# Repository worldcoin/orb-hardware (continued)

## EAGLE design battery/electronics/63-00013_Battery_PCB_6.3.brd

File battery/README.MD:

## Overview
Our exchangeable battery is responsible for powering the orb during the dayli operations. Key facts: 
* **Cell**: 8x 18650 Li-Ion cells 
* **Configuration**: 4SP2 (4 in series, 2 strings parallel)
* **Nominal voltage**: 14.8V
* **Capacity**: 96.48Wh
* **Charging interface**: USB-C
* **Other**: UN38.3 certified

## Mechanics

You can download the .stp-files [here](mechanics/download.sh).

Preview STP-File:

## Electronics

Preview battery circuit board:

## Bill of material structure
Part of our release is a drilled-down bill of material listing all the parts used in our device. 

The columns in that file are: 
* **Level**: Due to multiple assemblies in our device, we have a nested BOM. The level column tells you how deep this component is nested.
* **Item number**: Running number within the Assembly / Sub-Assembly
* **Partnumber**: Our internal part-number
* **Manufacturer P/N**: The part-number / unique name that our supplier uses as a part reference
* **Quantity**: Quantity of the part in the given assembly context

Please note that some parts have multiple entries in our BOM as each line lists the component in a different assembly context. 

## Directory Structure

    ├── Electronics         # Board and schematics
    ├── Mechanics           # STP-Files
    └── BOM                 # Bill of material   

## License

Copyright 2020-2023 The Worldcoin Foundation.

You may use this package under the Worldcoin Responsible Use License, version 1.0, or at your option, any later version. See the file [COPYING](../COPYING.md) for more details, and [LICENSE](../LICENSE.md) for the terms of the Worldcoin Responsible Use License, version 1.0.

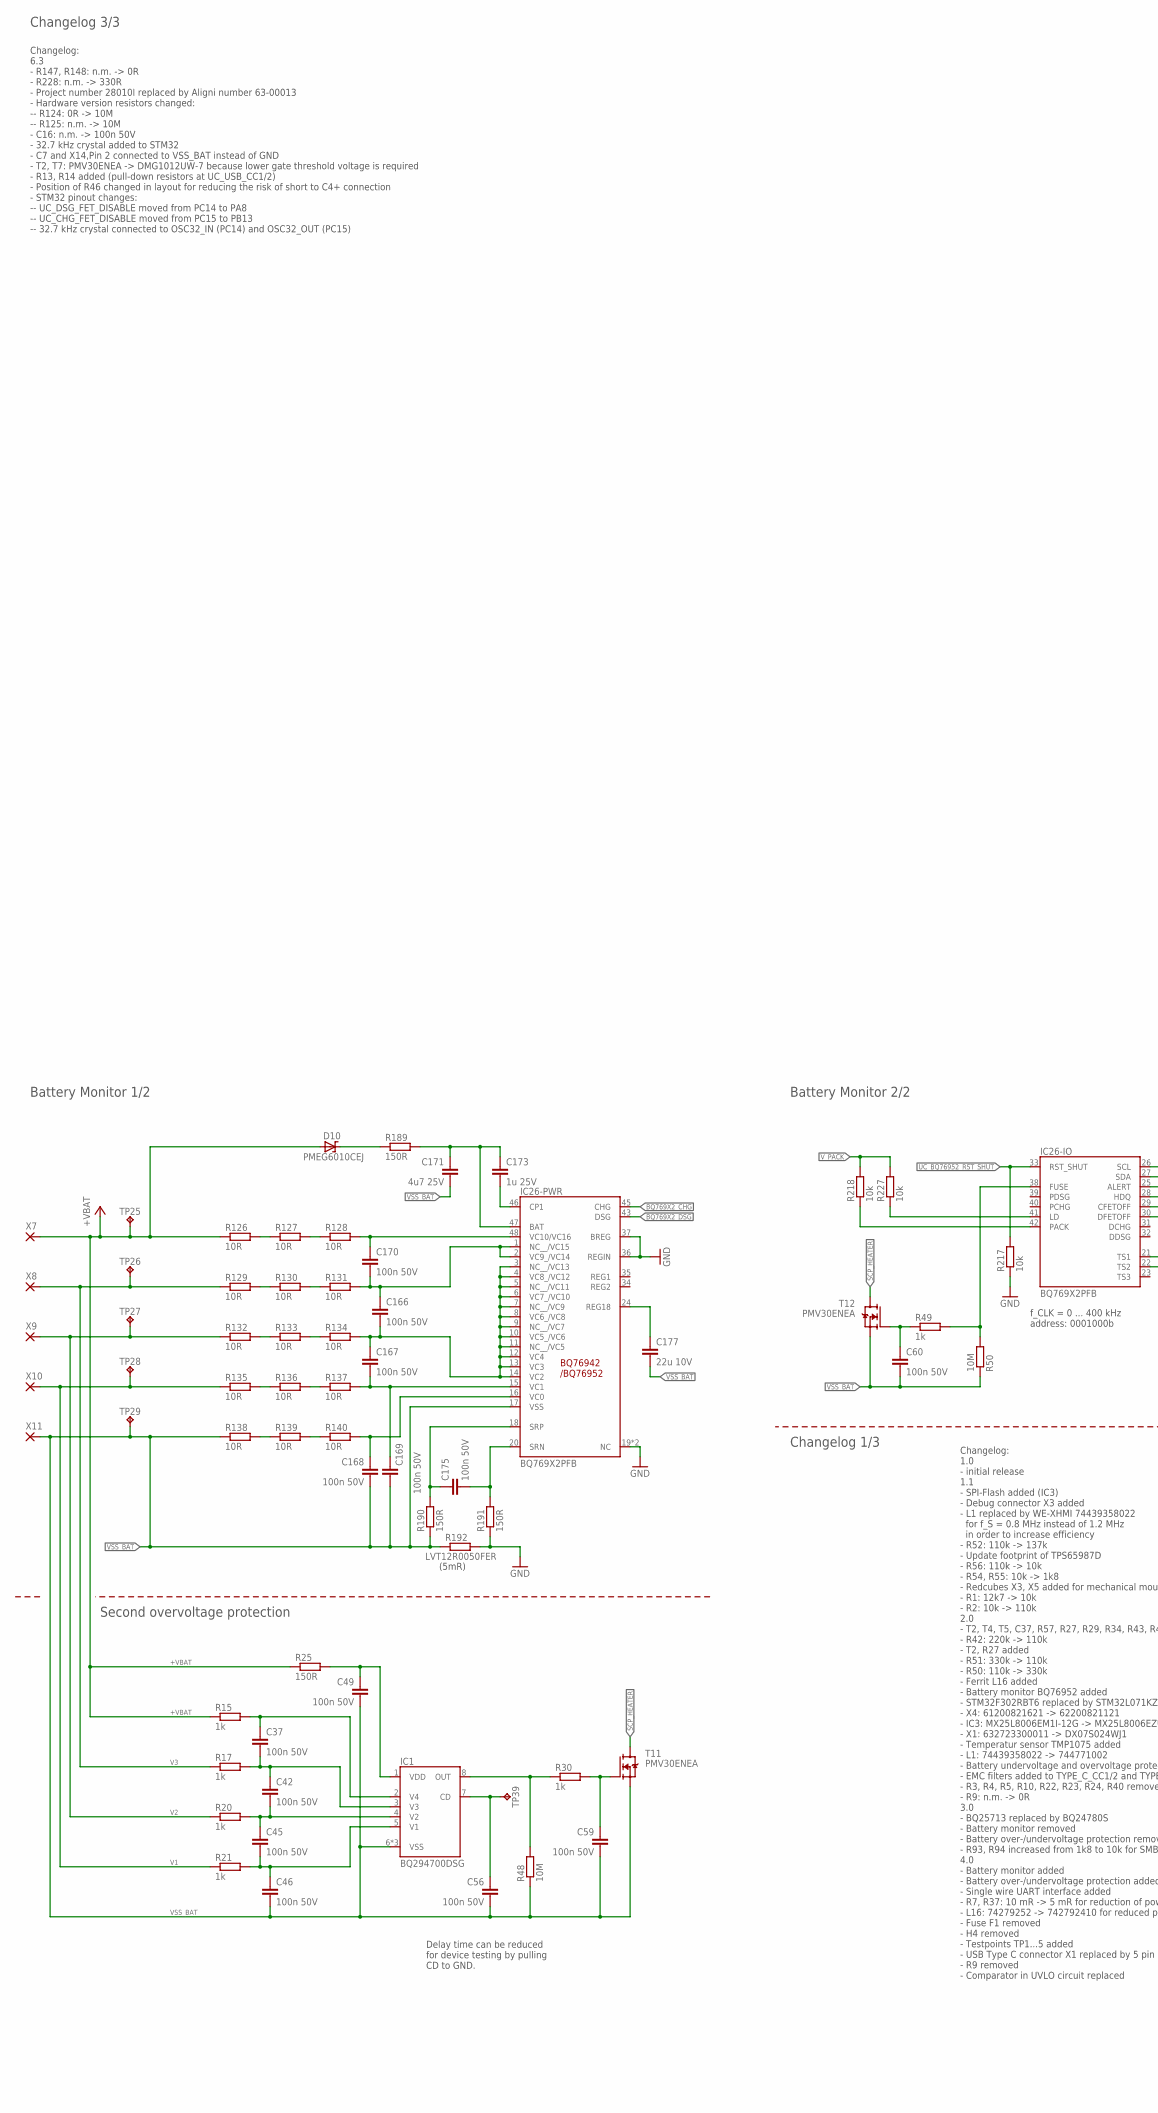
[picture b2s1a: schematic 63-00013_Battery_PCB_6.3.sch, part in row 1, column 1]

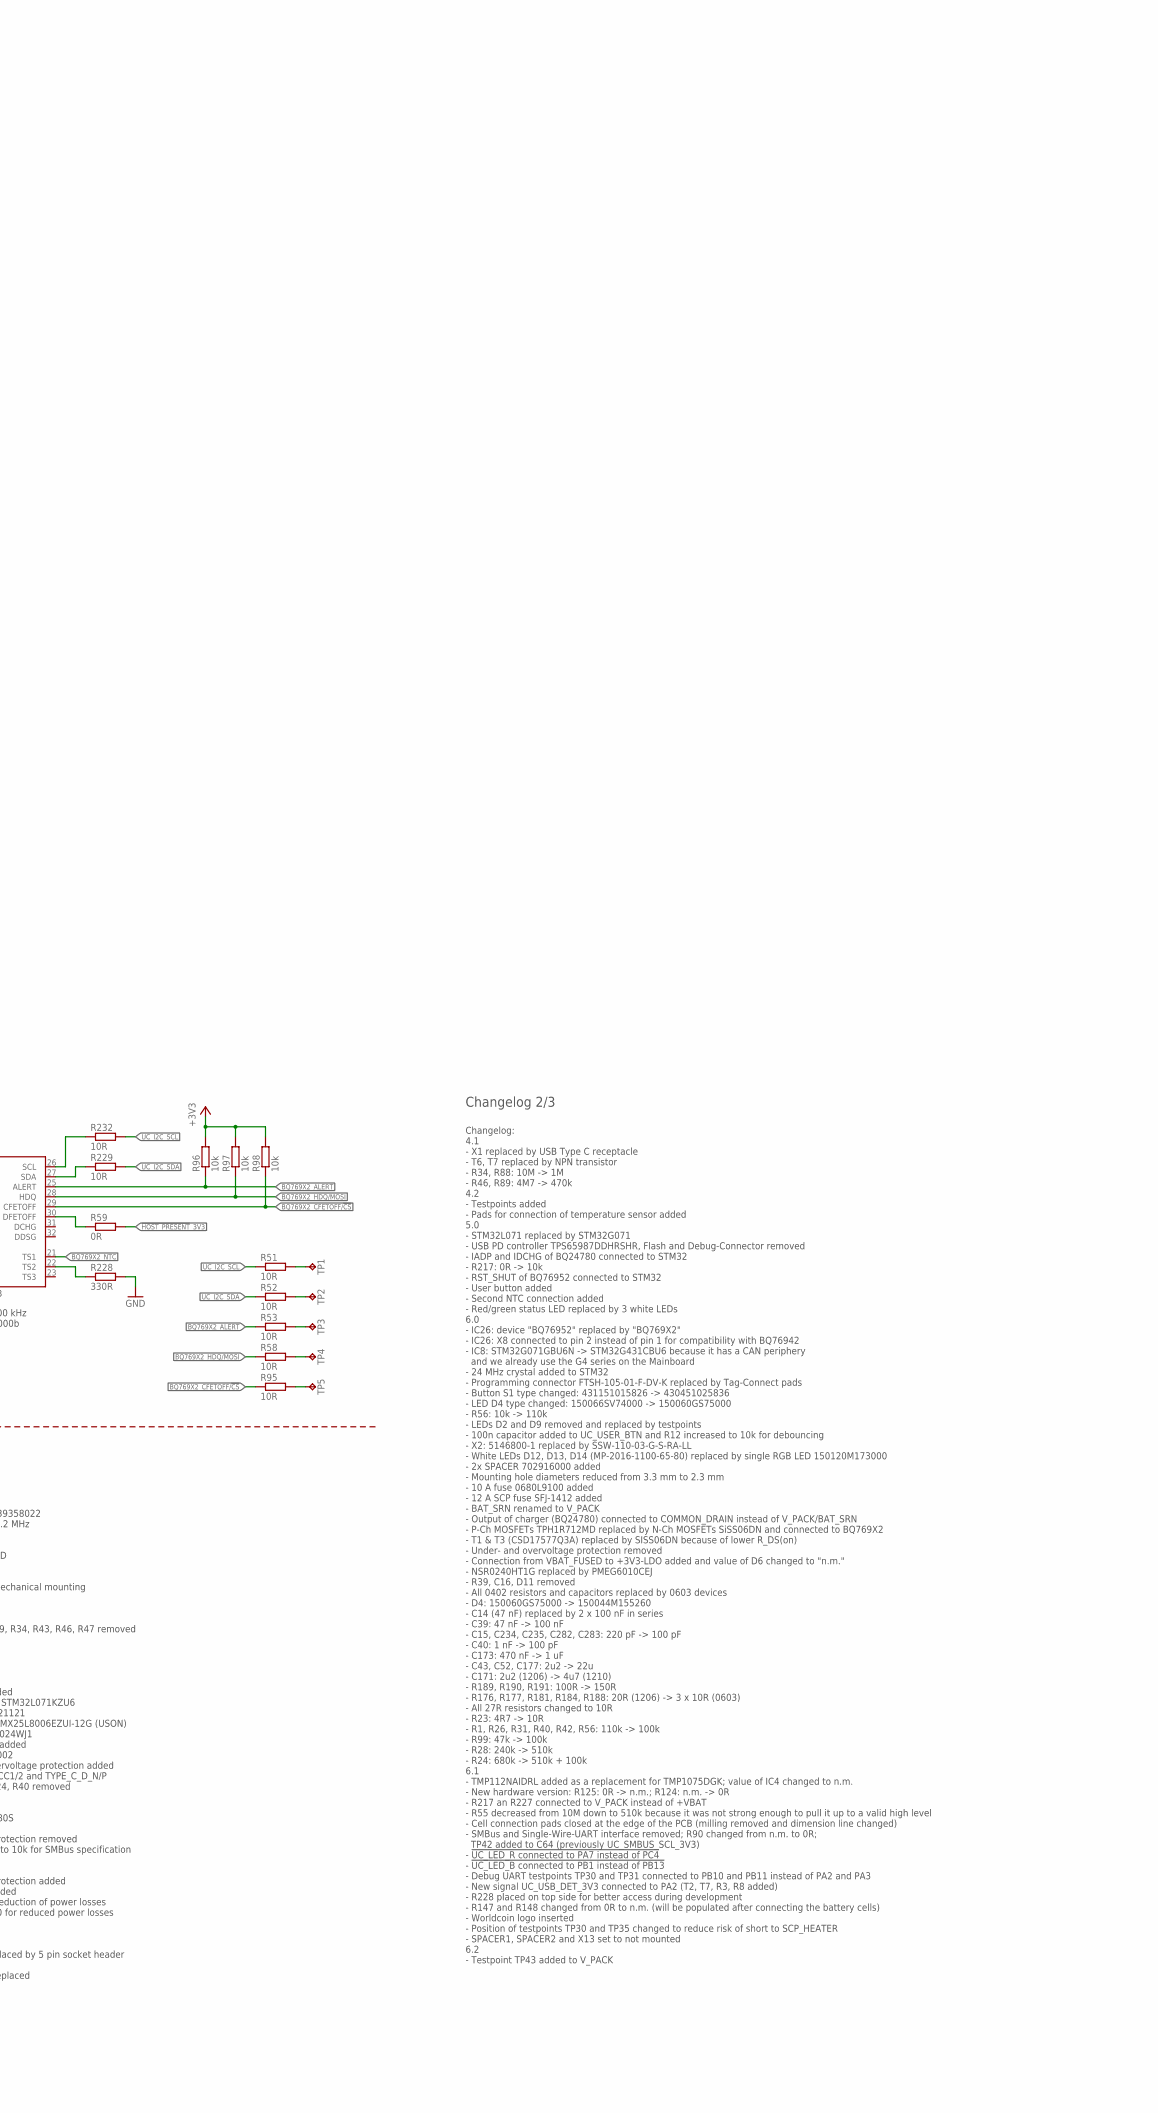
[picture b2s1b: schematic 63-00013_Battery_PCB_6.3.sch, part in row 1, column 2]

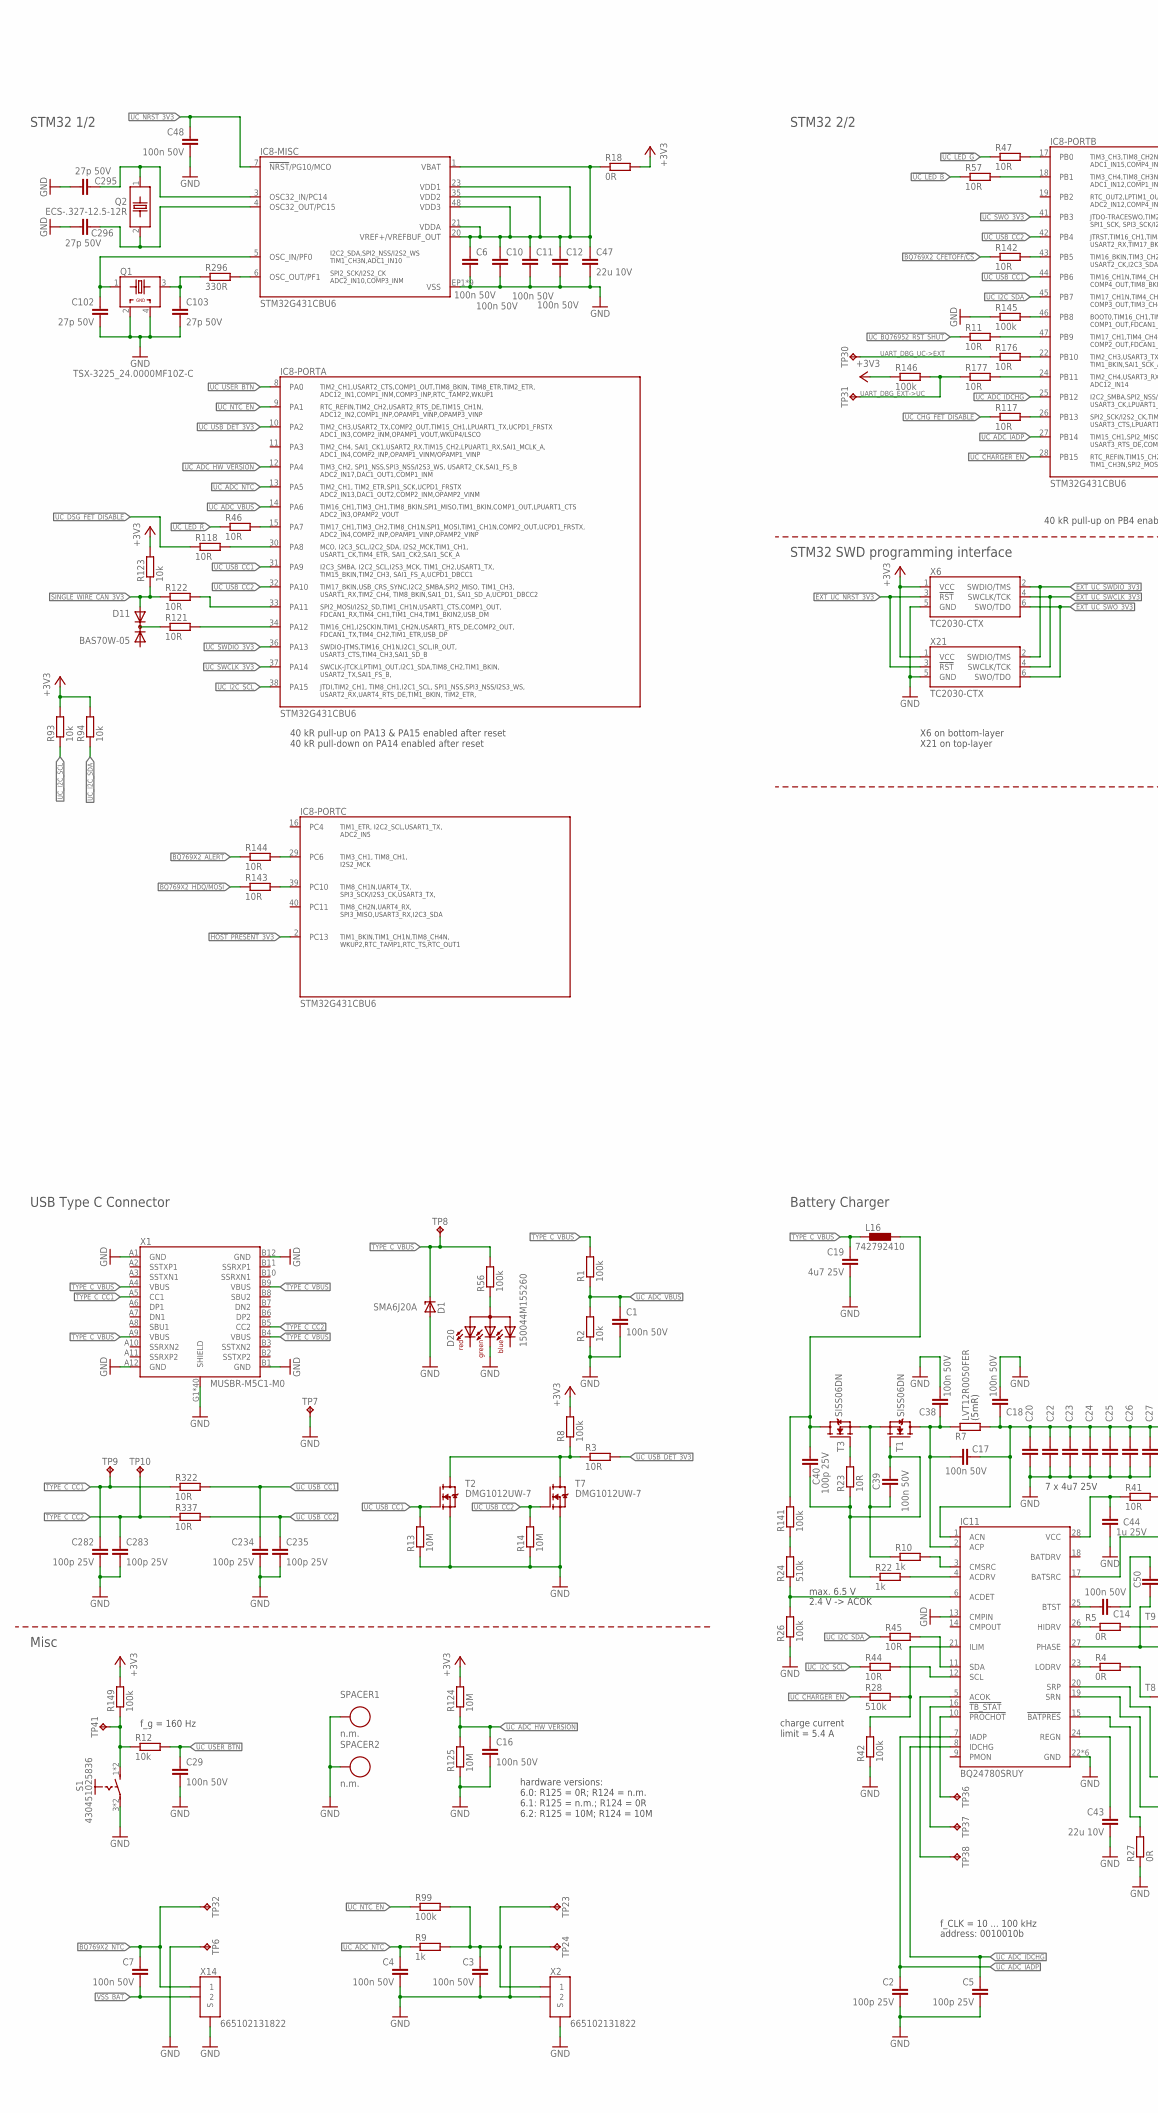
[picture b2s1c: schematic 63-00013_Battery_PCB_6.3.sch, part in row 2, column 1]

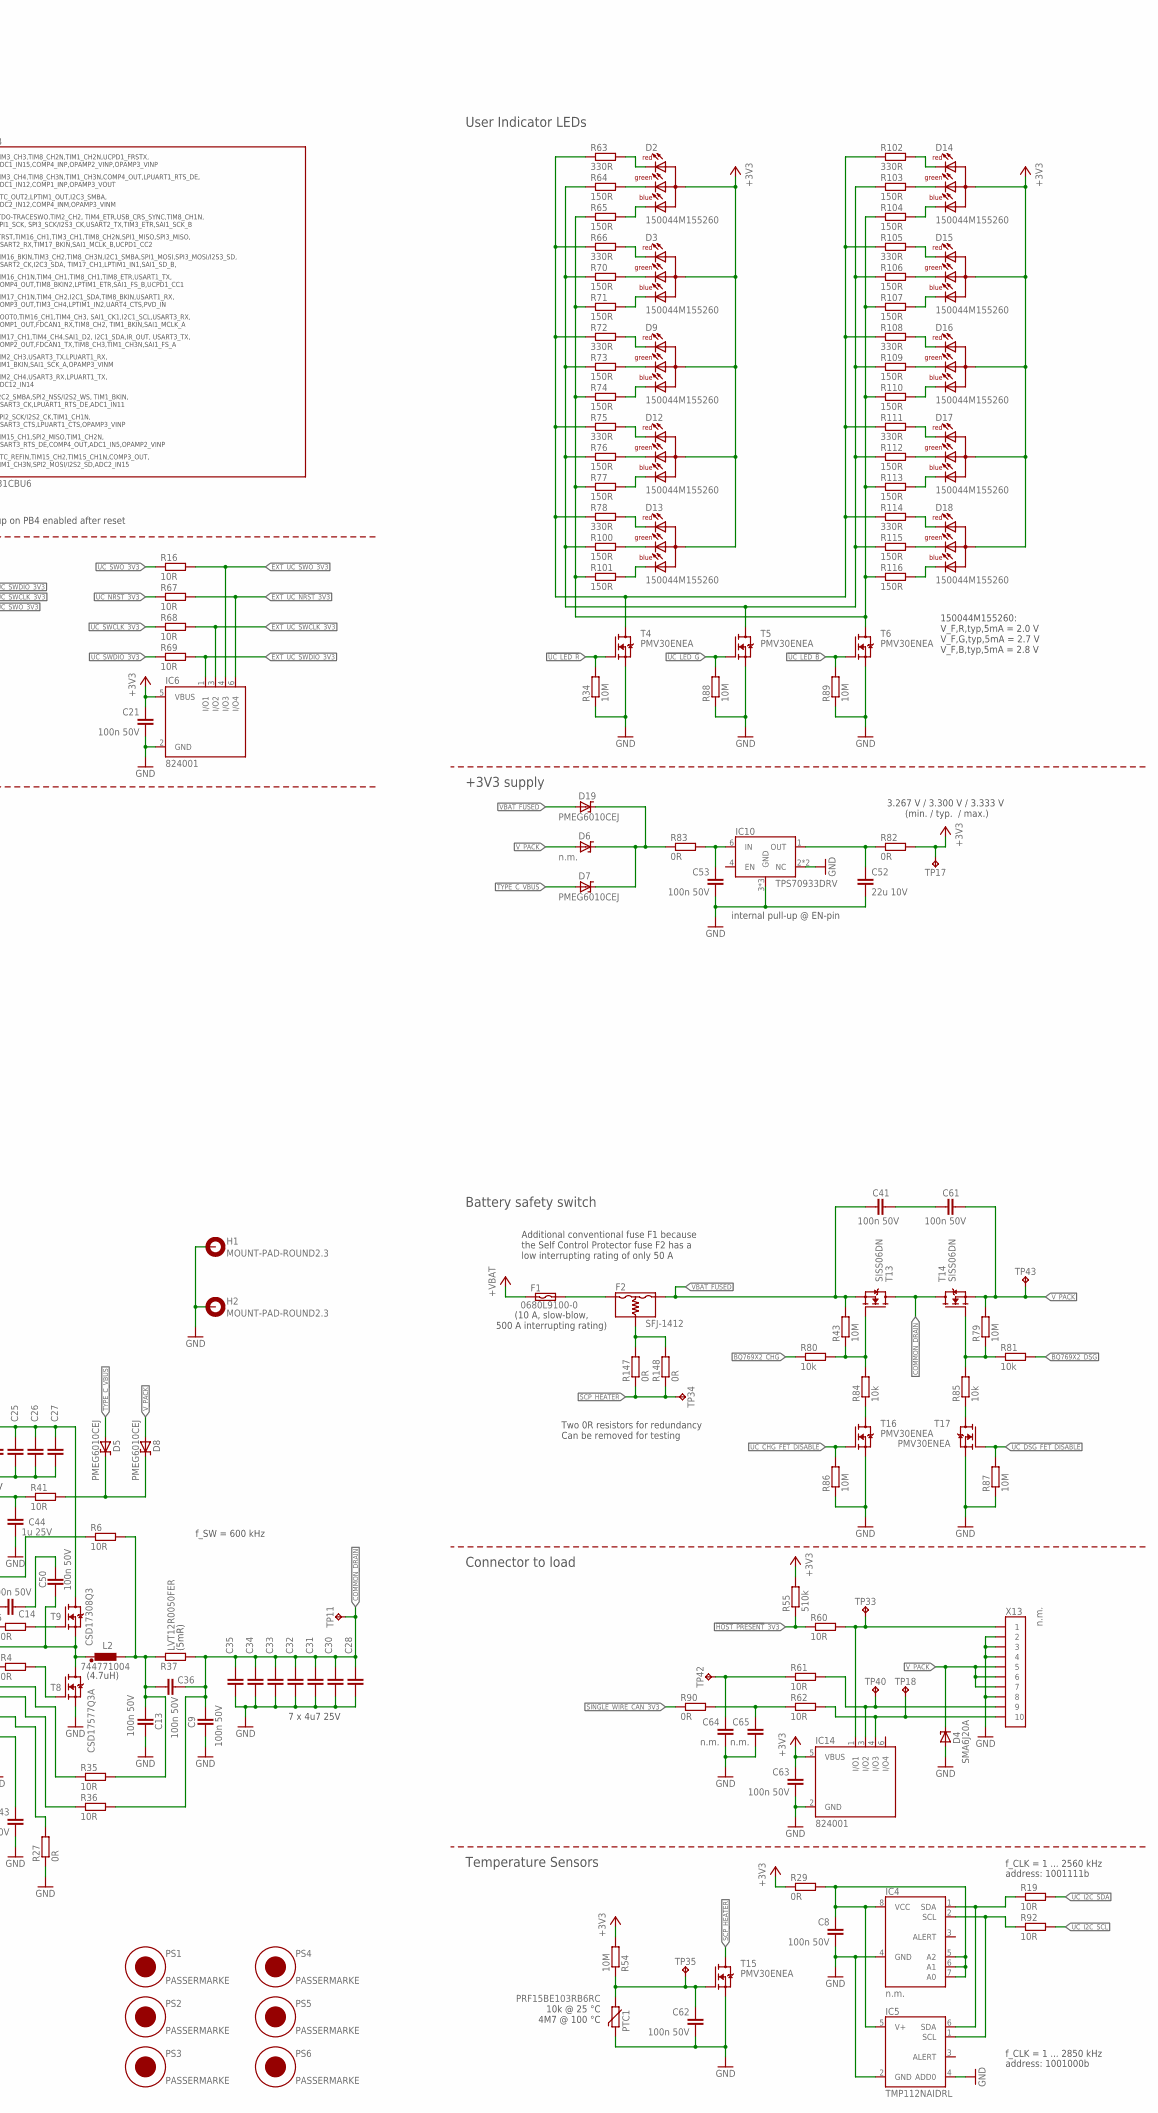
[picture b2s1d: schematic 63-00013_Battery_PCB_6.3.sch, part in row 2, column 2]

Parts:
C1, C3, C4, C6, C7, C8, C9, C10, C11, C12, C13, C14, C16, C17, C18, C21, C29, C36, C37, C38, C39, C41, C42, C45, C46, C48, C49, C50, C53, C56, C59, C60, C61, C62, C63, C166, C167, C168, C169, C170, C175: 100n 50V; C0603; VOLTAGE 50.0 V
C2, C5, C40, C234, C235, C282, C283: 100p 25V; C0603; VOLTAGE 25.0 V
C19, C20, C22, C23, C24, C25, C26, C27, C28, C30, C31, C32, C33, C34, C35, C171: 4u7 25V; C1210; VOLTAGE 25 V
C43, C47, C52, C177: 22u 10V; C0805; VOLTAGE 10.0 V
C44, C173: 1u 25V; C0805; VOLTAGE 25.0 V
C64, C65: n.m.; C0603; VOLTAGE 25.0 V
C102, C103, C295, C296: 27p 50V; C0603; VOLTAGE 50.0 V
D1, D4: SMA6J20A; SMA_ST
D2, D3, D9, D12, D13, D14, D15, D16, D17, D18, D20: 150044M155260; 150044M155260_WUERTH
D5, D7, D8, D10, D19: PMEG6010CEJ; SOD323F_SC-90_NXP
D6: n.m.; SOD323F_SC-90_NXP
D11: BAS70W-05; SOT-323_DIODES_INC
F1: 0680L9100-0; 0680L_BEL_FUSE
F2: SFJ-1412; SFJ-XX12_DEXERIALS
H1, H2: MOUNT-PAD-ROUND2.3; 2,3-PAD
IC1: BQ294700DSG; DSG0008A_WSON_TI
IC4: n.m.; S-PDSO-G8_DGK_VSSOP_TI
IC5: TMP112NAIDRL; DRL0006A_TI
IC6, IC14: 824001; SOT23-6L_WE
IC8: STM32G431CBU6; UFQFPN48_ST
IC10: TPS70933DRV; DRV0006A_TI
IC11: BQ24780SRUY; RUY0028A_TI
IC26: BQ769X2PFB; S-PQFP-G48_PFB_TI
L2: 744771004; WE-PD_1260_WE
L16: 742792410; FERRIT_1806_WUERTH
PS1, PS2, PS3, PS4, PS5, PS6: PASSERMARKE
PTC1: PRF15BE103RB6RC; R0402
Q1: TSX-3225_24.0000MF10Z-C; TSX-3225_SEIKO_EPSON
Q2: ECS-.327-12.5-12R; ECX-12R_ECS
R1, R8, R26, R42, R56, R99, R141, R145, R146, R149: 100k; R0603
R2, R12, R80, R81, R84, R85, R93, R94, R96, R97, R98, R123, R217, R218, R227: 10k; R0603
R3, R6, R11, R16, R19, R23, R35, R36, R41, R44, R45, R46, R47, R51, R52, R53, R57, R58, R60, R61, R62, R67, R68, R69, R92, R95, R117, R118, R121, R122, R126, R127, R128, R129, R130, R131, R132, R133, R134, R135, R136, R137, R138, R139, R140, R142, R143, R144, R176, R177, R229, R232, R322, R337: 10R; R0603
R4, R5, R18, R27, R29, R59, R82, R83, R90, R147, R148: 0R; R0603
R7, R37, R192: LVT12R0050FER; LVT12_R003_OHMITE
R9, R10, R15, R17, R20, R21, R22, R30, R49: 1k; R0603
R13, R14, R34, R43, R48, R50, R54, R79, R86, R87, R88, R89, R124, R125: 10M; R0603
R24, R28, R55: 510k; R0603
R25, R64, R65, R70, R71, R73, R74, R76, R77, R100, R101, R103, R104, R106, R107, R109, R110, R112, R113, R115, R116, R189, R190, R191: 150R; R0603
R63, R66, R72, R75, R78, R102, R105, R108, R111, R114, R228, R296: 330R; R0603
S1: 430451025836; 430451025836_WUERTH
SPACER1, SPACER2: n.m.; 702916000_WUERTH
T1, T3, T13, T14: SISS06DN; POWERPAK_1212-8S_VISHAY
T2, T7: DMG1012UW-7; SOT-323_DIODES_INC
T4, T5, T6, T11, T12, T15, T16, T17: PMV30ENEA; SOT-23_NXP
T8: CSD17577Q3A; Q3A_TI
T9: CSD17308Q3; Q3_TI
TP1, TP2, TP3, TP4, TP5, TP6, TP7, TP8, TP9, TP10, TP11, TP17, TP18, TP23, TP24, TP25, TP26, TP27, TP28, TP29, TP30, TP31, TP32, TP33, TP34, TP35, TP36, TP37, TP38, TP39, TP40, TP41, TP42, TP43: TESTPOINT_VIA_ROUND_0.8MM; TESTVIA_ROUND_0.8MM
X1: MUSBR-M5C1-M0; MUSBR-M5C1-XX_AMPHENOL
X2, X14: 665102131822; 665102131822_WURTH
X6, X21: TC2030-CTX; TC2030-IDC-FP_TAGCONNECT
X7, X8, X9, X10, X11: WIREPAD_0.8X6.5MM
X13: n.m.; SSW-110-03-G-S-RA-LL_SAMTEC

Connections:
!HOST_PRESENT!_3V3: IC8.2 (PC13), R55.1, R59.2, R60.1
!LED_B: R65.1, R71.1, R74.1, R77.1, R101.1, R104.1, R107.1, R110.1, R113.1, R116.1, T6.3 (D)
!LED_G: R64.1, R70.1, R73.1, R76.1, R100.1, R103.1, R106.1, R109.1, R112.1, R115.1, T5.3 (D)
!LED_R: R63.1, R66.1, R72.1, R75.1, R78.1, R102.1, R105.1, R108.1, R111.1, R114.1, T4.3 (D)
!UC_LED_B: R57.1, R89.2, T6.1 (G)
!UC_LED_G: R47.1, R88.2, T5.1 (G)
!UC_LED_R: R34.2, R46.1, T4.1 (G)
+3V3: C21.1, C63.1, D2.1 (A), D3.1 (A), D9.1 (A), D12.1 (A), D13.1 (A), D14.1 (A), D15.1 (A), D16.1 (A), D17.1 (A), D18.1 (A), IC6.5 (VBUS), IC14.5 (VBUS), R8.2, R18.2, R29.1, R54.2, R55.2, R82.2, R93.2, R94.2, R96.2, R97.2, R98.2, R123.2, R124.2, R146.1, R149.2, TP17.P$1, X6.1 (VCC), X21.1 (VCC)
+VBAT: D10.A, F1.1, R15.1, R25.1, R126.1, TP25.P$1, X7.P$1, X7.P$2, X7.P$3, X7.P$4, X7.P$5, X7.P$6, X7.P$7, X7.P$8, X7.P$9, X7.P$10, X7.P$11, X7.P$12, X7.P$13, X7.P$14, X7.P$15, X7.P$16, X7.P$17, X7.P$18, X7.P$19, X7.P$20, X7.P$21, X7.P$22, X7.P$23, X7.P$24, X7.P$25, X7.P$26, X7.P$27, X7.P$28, X7.P$29, X7.P$30, X7.P$31, X7.P$32, X7.P$33, X7.P$34, X7.P$35, X7.P$36, X7.P$37, X7.P$38, X7.P$39, X7.P$40, X7.P$41, X7.P$42, X7.P$43, X7.P$44, X7.P$45, X7.P$46, X7.P$47, X7.P$48, X7.P$49, X7.P$50, X7.P$51, X7.P$52, X7.P$53, X7.P$54, X7.P$55, X7.P$56, X7.P$57, X7.P$58, X7.P$59, X7.P$60, X7.P$61, X7.P$62, X7.P$63, X7.P$64, X7.P$65, X7.P$66, X7.P$67
BQ769X2_ALERT: IC26.25 (ALERT), R53.1, R96.1, R144.1
BQ769X2_CFETOFF/!CS: IC26.29 (CFETOFF), R95.1, R98.1, R142.1
BQ769X2_CHG: IC26.45 (CHG), R80.1
BQ769X2_DSG: IC26.43 (DSG), R81.2
BQ769X2_HDQ/MOSI: IC26.28 (HDQ), R58.1, R97.1, R143.1
BQ769X2_NTC: C7.1, IC26.21 (TS1), TP32.P$1, X14.1
CHARGER_VCC: D6.C, D7.C, D19.C, R83.1
COMMON_DRAIN: C9.1, C28.1, C30.1, C31.1, C32.1, C33.1, C34.1, C35.1, C36.2, R36.2, R37.2, T13.5 (D), T14.5 (D), TP11.P$1
EXT_UC_NRST_3V3: IC6.6 (I/O4), R67.2, X6.3 (!RST), X21.3 (!RST)
EXT_UC_SWCLK_3V3: IC6.3 (I/O2), R68.2, X6.4 (SWCLK/TCK), X21.4 (SWCLK/TCK)
EXT_UC_SWDIO_3V3: IC6.1 (I/O1), R69.2, X6.2 (SWDIO/TMS), X21.2 (SWDIO/TMS)
EXT_UC_SWO_3V3: IC6.4 (I/O3), R16.2, X6.6 (SWO/TDO), X21.6 (SWO/TDO)
GND: C1.2, C2.2, C3.2, C4.2, C5.2, C6.2, C8.2, C9.2, C10.2, C11.2, C12.2, C13.2, C16.2, C18.1, C19.2, C20.2, C21.2, C22.2, C23.2, C24.2, C25.2, C26.2, C27.2, C28.2, C29.2, C30.2, C31.2, C32.2, C33.2, C34.2, C35.2, C38.1, C43.2, C44.2, C47.2, C48.2, C52.2, C53.2, C62.2, C63.2, C64.2, C65.2, C102.2, C103.2, C234.2, C235.2, C282.2, C283.2, C295.2, C296.2, D1.A, D4.A, D20.3 (C_GREEN), H1.B2,3, H2.B2,3, IC4.4 (GND), IC5.2 (GND), IC5.4 (ADD0), IC6.2 (GND), IC8.EP1 (VSS), IC8.EP2 (VSS), IC8.EP3 (VSS), IC8.EP4 (VSS), IC8.EP5 (VSS), IC8.EP6 (VSS), IC8.EP7 (VSS), IC8.EP8 (VSS), IC8.EP9 (VSS), IC10.2 (NC), IC10.3 (GND), IC10.5 (NC), IC10.7.1 (GND), IC10.7.2 (GND), IC11.13 (CMPIN), IC11.22 (GND), IC11.E1 (GND), IC11.E2 (GND), IC11.E3 (GND), IC11.E4 (GND), IC11.E5 (GND), IC14.2 (GND), IC26.19 (NC), IC26.36 (REGIN), IC26.37 (BREG), IC26.44 (NC), PTC1.1, Q1.2 (G1), Q1.4 (G2), R2.1, R13.1, R14.1, R26.1, R27.1, R34.1, R42.1, R86.1, R87.1, R88.1, R89.1, R125.1, R145.1, R191.1, R192.2, R217.1, R228.2, S1.3, S1.4, SPACER1.P$1, SPACER2.P$1, T2.2 (S), T4.2 (S), T5.2 (S), T6.2 (S), T7.2 (S), T8.1 (S), T8.2 (S), T8.3 (S), T15.2 (S), T16.2 (S), T17.2 (S), TP6.P$1, TP7.P$1, TP24.P$1, X1.A1 (GND), X1.A12 (GND), X1.B1 (GND), X1.B12 (GND), X1.G1 (SHIELD), X1.G2 (SHIELD), X1.G3 (SHIELD), X1.G4 (SHIELD), X1.G5 (SHIELD), X1.G6 (SHIELD), X1.S1 (SHIELD), X1.S2 (SHIELD), X1.S3 (SHIELD), X1.S4 (SHIELD), X1.S5 (SHIELD), X1.S6 (SHIELD), X1.S7 (SHIELD), X1.S8 (SHIELD), X1.S9 (SHIELD), X1.S10 (SHIELD), X1.S11 (SHIELD), X1.S12 (SHIELD), X1.S13 (SHIELD), X1.S14 (SHIELD), X1.S15 (SHIELD), X1.S16 (SHIELD), X1.S17 (SHIELD), X1.S18 (SHIELD), X1.S19 (SHIELD), X1.S20 (SHIELD), X1.S21 (SHIELD), X1.S22 (SHIELD), X1.S23 (SHIELD), X1.S24 (SHIELD), X1.S25 (SHIELD), X1.S26 (SHIELD), X1.S27 (SHIELD), X1.S28 (SHIELD), X1.S29 (SHIELD), X1.S30 (SHIELD), X1.S31 (SHIELD), X1.S32 (SHIELD), X1.S33 (SHIELD), X1.S34 (SHIELD), X2.2, X2.S1 (S), X2.S2 (S), X6.5 (GND), X13.2, X13.3, X13.4, X13.8, X14.S1 (S), X14.S2 (S), X21.5 (GND)
unnamed: C64.1, R61.1, TP42.P$1
unnamed: D5.C, D8.C, R41.2
unnamed: R12.1, R149.1, S1.1 (S), S1.2 (S), TP41.P$1
unnamed: IC8.15 (PA7), R46.2
unnamed: IC8.47 (PB9), R11.2
unnamed: IC8.18 (PB1), R57.2
unnamed: D11.3 (C), R121.1
unnamed: C103.1, Q1.3 (C2), R296.1
unnamed: IC11.10 (!PROCHOT), TP36.P$1
unnamed: IC11.16 (!TB_STAT), TP37.P$1
unnamed: IC11.5 (ACOK), TP38.P$1
unnamed: C45.2, C46.1, IC1.5 (V1), R21.2
unnamed: C42.2, C45.1, IC1.4 (V2), R20.2
unnamed: C37.2, C42.1, IC1.3 (V3), R17.2
unnamed: C37.1, IC1.2 (V4), R15.2
unnamed: C49.1, IC1.1 (VDD), R25.2
unnamed: C56.1, IC1.7 (CD), TP39.P$1
unnamed: IC1.8 (OUT), R30.1, R48.2
unnamed: F1.2, F2.T1 (F1)
unnamed: C59.1, R30.2, T11.1 (G)
unnamed: C14.2, IC11.25 (BTST)
unnamed: C60.1, R49.1, T12.1 (G)
unnamed: IC4.2 (SCL), IC5.1 (SCL), R92.1
unnamed: IC11.17 (BATSRC), R6.1
unnamed: C17.1, C38.2, IC11.2 (ACP), R7.1, T1.5 (D)
unnamed: C13.1, C36.1, L2.NODOT, R6.2, R35.2, R37.1
unnamed: C17.2, C18.2, C20.1, C22.1, C23.1, C24.1, C25.1, C26.1, C27.1, IC11.1 (ACN), R7.2, T9.5 (D), T9.P$1 (D), T9.P$4 (D), T9.P$5 (D), T9.P$6 (D), T9.P$7 (D)
unnamed: IC11.4 (ACDRV), R22.2
unnamed: IC11.3 (CMSRC), R10.2
unnamed: C39.1, R10.1, T1.1 (S), T1.2 (S), T1.3 (S), T3.1 (S), T3.2 (S), T3.3 (S)
unnamed: C39.2, C40.1, R22.1, R23.1, T1.4 (G)
unnamed: IC26.38 (FUSE), R49.2, R50.2
unnamed: C8.1, IC4.5 (A2), IC4.6 (A1), IC4.7 (A0), IC4.8 (VCC), IC5.5 (V+), R29.2
unnamed: C62.1, PTC1.2, R54.1, T15.1 (G), TP35.P$1
unnamed: IC26.30 (DFETOFF), R59.1
unnamed: C40.2, L16.1, R141.2, T3.5 (D)
unnamed: C41.1, C61.2
unnamed: IC14.1 (I/O1), R60.2, TP33.P$1, X13.1
unnamed: C6.1, C10.1, C11.1, C12.1, C47.1, IC8.1 (VBAT), IC8.20 (VREF+/VREFBUF_OUT), IC8.21 (VDDA), IC8.23 (VDD1), IC8.35 (VDD2), IC8.48 (VDD3), R18.1
unnamed: IC11.19 (SRN), R36.1
unnamed: IC11.20 (SRP), R35.1
unnamed: R5.2, T9.4 (G)
unnamed: R23.2, T3.4 (G)
unnamed: IC11.12 (SCL), R44.2
unnamed: IC11.11 (SDA), R45.2
unnamed: IC11.6 (ACDET), R24.1, R26.2
unnamed: IC11.21 (ILIM), R28.2, R42.2
unnamed: IC14.3 (I/O2), R61.2, TP40.P$1, X13.9
unnamed: IC14.4 (I/O3), R62.2, TP18.P$1, X13.10
unnamed: IC11.15 (!BATPRES), R27.2
unnamed: C50.2, IC11.27 (PHASE), L2.DOT, T8.5 (D), T8.P$1 (D), T8.P$2 (D), T8.P$3 (D), T8.P$4 (D), T8.P$5 (D), T8.P$6 (D), T8.P$7 (D), T9.1 (S), T9.2 (S), T9.3 (S)
unnamed: IC8.34 (PA12), R121.2
unnamed: C44.1, IC11.28 (VCC), R41.1
unnamed: C65.1, R62.1, R90.2
unnamed: C43.1, IC11.24 (REGN)
unnamed: C168.1, IC26.16 (VC0), R140.2
unnamed: C177.1, IC26.24 (REG18)
unnamed: IC8.22 (PB10), R176.2
unnamed: IC8.24 (PB11), R177.2
unnamed: IC8.33 (PA11), R122.2
unnamed: D2.3 (C_GREEN), R64.2
unnamed: D2.2 (C_RED), R63.2
unnamed: D20.1 (A), R56.1
unnamed: R127.2, R128.1
unnamed: R43.1, R80.2, R84.2, T13.4 (G)
unnamed: D2.4 (C_BLUE), R65.2
unnamed: D3.3 (C_GREEN), R70.2
unnamed: D3.2 (C_RED), R66.2
unnamed: D3.4 (C_BLUE), R71.2
unnamed: D9.3 (C_GREEN), R73.2
unnamed: D9.2 (C_RED), R72.2
unnamed: D9.4 (C_BLUE), R74.2
unnamed: R79.1, R81.1, R85.2, T14.4 (G)
unnamed: C52.1, IC10.1 (OUT), R82.1
unnamed: C53.1, IC10.6 (IN), R83.2
unnamed: R85.1, T17.3 (D)
unnamed: R84.1, T16.3 (D)
unnamed: C14.1, C50.1
unnamed: R126.2, R127.1
unnamed: IC4.1 (SDA), IC5.6 (SDA), R19.1
unnamed: R130.2, R131.1
unnamed: IC11.26 (HIDRV), R5.1
unnamed: IC11.23 (LODRV), R4.1
unnamed: R4.2, T8.4 (G)
unnamed: R95.2, TP5.P$1
unnamed: R58.2, TP4.P$1
unnamed: R53.2, TP3.P$1
unnamed: R52.2, TP2.P$1
unnamed: R51.2, TP1.P$1
unnamed: C3.1, R9.2, R99.2, TP23.P$1, X2.1
unnamed: D12.3 (C_GREEN), R76.2
unnamed: R129.2, R130.1
unnamed: D12.2 (C_RED), R75.2
unnamed: D12.4 (C_BLUE), R77.2
unnamed: D13.3 (C_GREEN), R100.2
unnamed: D13.2 (C_RED), R78.2
unnamed: D13.4 (C_BLUE), R101.2
unnamed: D14.3 (C_GREEN), R103.2
unnamed: D14.2 (C_RED), R102.2
unnamed: D14.4 (C_BLUE), R104.2
unnamed: D15.3 (C_GREEN), R106.2
unnamed: D15.2 (C_RED), R105.2
unnamed: D15.4 (C_BLUE), R107.2
unnamed: D16.3 (C_GREEN), R109.2
unnamed: D16.2 (C_RED), R108.2
unnamed: D16.4 (C_BLUE), R110.2
unnamed: D17.3 (C_GREEN), R112.2
unnamed: D17.2 (C_RED), R111.2
unnamed: D17.4 (C_BLUE), R113.2
unnamed: D18.3 (C_GREEN), R115.2
unnamed: D18.2 (C_RED), R114.2
unnamed: D18.4 (C_BLUE), R116.2
unnamed: R133.2, R134.1
unnamed: R132.2, R133.1
unnamed: R136.2, R137.1
unnamed: R135.2, R136.1
unnamed: R139.2, R140.1
unnamed: R138.2, R139.1
unnamed: R24.2, R141.1
unnamed: IC8.46 (PB8), R145.2
unnamed: F2.T2 (H), R147.2, R148.2
unnamed: R3.1, R8.1, T2.3 (D), T7.3 (D)
unnamed: IC8.30 (PA8), R118.2
unnamed: IC8.26 (PB13), R117.2
unnamed: IC8.17 (PB0), R47.2
unnamed: IC8.43 (PB5), R142.2
unnamed: IC8.39 (PC10), R143.2
unnamed: IC8.29 (PC6), R144.2
unnamed: C166.2, C167.1, IC26.3 (NC__/VC13), IC26.4 (VC8_/VC12), IC26.5 (NC__/VC11), IC26.6 (VC7_/VC10), IC26.7 (NC__/VC9), IC26.8 (VC6_/VC8), IC26.9 (NC__/VC7), IC26.10 (VC5_/VC6), IC26.11 (NC__/VC5), IC26.12 (VC4), IC26.13 (VC3), IC26.14 (VC2), R134.2
unnamed: C166.1, C170.2, IC26.1 (NC__/VC15), IC26.2 (VC9_/VC14), R131.2
unnamed: C167.2, C169.1, IC26.15 (VC1), R137.2
unnamed: C170.1, IC26.48 (VC10/VC16), R128.2
unnamed: C102.1, IC8.5 (OSC_IN/PF0), Q1.1 (C1)
unnamed: C173.2, IC26.46 (CP1)
unnamed: D10.C, R189.1
unnamed: C171.1, C173.1, IC26.47 (BAT), R189.2
unnamed: C175.1, IC26.18 (SRP), R190.2
unnamed: C175.2, IC26.20 (SRN), R191.2
unnamed: IC8.6 (OSC_OUT/PF1), R296.2
unnamed: IC26.27 (SDA), R229.1
unnamed: IC26.26 (SCL), R232.1
unnamed: IC26.41 (LD), R227.1
unnamed: IC26.42 (PACK), R218.1
unnamed: IC26.22 (TS2), R228.1
unnamed: C296.1, IC8.4 (OSC32_OUT/PC15), Q2.2
unnamed: C295.1, IC8.3 (OSC32_IN/PC14), Q2.1
SCP_HEATER: R147.1, R148.1, T11.3 (D), T12.3 (D), T15.3 (D), TP34.P$1
SINGLE_WIRE_CAN_3V3: D11.2 (A2), R90.1, R122.1, R123.1
TYPE_C_CC1: C282.1, R322.1, TP9.P$1, X1.A5 (CC1)
TYPE_C_CC2: C283.1, R337.1, TP10.P$1, X1.B5 (CC2)
TYPE_C_VBUS: C19.1, D1.C, D5.A, D7.A, L16.2, R1.2, R56.2, TP8.P$1, X1.A4 (VBUS), X1.A9 (VBUS), X1.B4 (VBUS), X1.B9 (VBUS)
UART_DBG_EXT->UC: R146.2, R177.1, TP31.P$1
UART_DBG_UC->EXT: R176.1, TP30.P$1
UC_ADC_HW_VERSION: C16.1, IC8.12 (PA4), R124.1, R125.2
UC_ADC_IADP: C2.1, IC8.27 (PB14), IC11.7 (IADP)
UC_ADC_IDCHG: C5.1, IC8.25 (PB12), IC11.8 (IDCHG)
UC_ADC_NTC: C4.1, IC8.13 (PA5), R9.1
UC_ADC_VBUS: C1.1, IC8.14 (PA6), R1.1, R2.2
UC_BQ76952_RST_SHUT: IC26.33 (RST_SHUT), R11.1, R217.2
UC_CHARGER_EN: IC8.28 (PB15), R28.1
UC_CHG_FET_DISABLE: R86.2, R117.1, T16.1 (G)
UC_DSG_FET_DISABLE: R87.2, R118.1, T17.1 (G)
UC_I2C_SCL: IC8.38 (PA15), R44.1, R51.1, R92.2, R93.1, R232.2
UC_I2C_SDA: IC8.45 (PB7), R19.2, R45.1, R52.1, R94.1, R229.2
UC_NRST_3V3: C48.1, IC8.7 (!NRST!/PG10/MCO), R67.1
UC_NTC_EN: IC8.9 (PA1), R99.1
UC_SWCLK_3V3: IC8.37 (PA14), R68.1
UC_SWDIO_3V3: IC8.36 (PA13), R69.1
UC_SWO_3V3: IC8.41 (PB3), R16.1
UC_USB_CC1: C234.1, IC8.31 (PA9), IC8.44 (PB6), R13.2, R322.2, T2.1 (G)
UC_USB_CC2: C235.1, IC8.32 (PA10), IC8.42 (PB4), R14.2, R337.2, T7.1 (G)
UC_USB_DET_3V3: IC8.10 (PA2), R3.2
UC_USER_BTN: C29.1, IC8.8 (PA0), R12.2
V1: R21.1, R135.1, TP28.P$1, X10.P$1, X10.P$2, X10.P$3, X10.P$4, X10.P$5, X10.P$6, X10.P$7, X10.P$8, X10.P$9, X10.P$10, X10.P$11, X10.P$12, X10.P$13, X10.P$14, X10.P$15, X10.P$16, X10.P$17, X10.P$18, X10.P$19, X10.P$20, X10.P$21, X10.P$22, X10.P$23, X10.P$24, X10.P$25, X10.P$26, X10.P$27, X10.P$28, X10.P$29, X10.P$30, X10.P$31, X10.P$32, X10.P$33, X10.P$34, X10.P$35, X10.P$36, X10.P$37, X10.P$38, X10.P$39, X10.P$40, X10.P$41, X10.P$42, X10.P$43, X10.P$44, X10.P$45, X10.P$46, X10.P$47, X10.P$48, X10.P$49, X10.P$50, X10.P$51, X10.P$52, X10.P$53, X10.P$54, X10.P$55, X10.P$56, X10.P$57, X10.P$58, X10.P$59, X10.P$60, X10.P$61, X10.P$62, X10.P$63, X10.P$64, X10.P$65, X10.P$66, X10.P$67
V2: R20.1, R132.1, TP27.P$1, X9.P$1, X9.P$2, X9.P$3, X9.P$4, X9.P$5, X9.P$6, X9.P$7, X9.P$8, X9.P$9, X9.P$10, X9.P$11, X9.P$12, X9.P$13, X9.P$14, X9.P$15, X9.P$16, X9.P$17, X9.P$18, X9.P$19, X9.P$20, X9.P$21, X9.P$22, X9.P$23, X9.P$24, X9.P$25, X9.P$26, X9.P$27, X9.P$28, X9.P$29, X9.P$30, X9.P$31, X9.P$32, X9.P$33, X9.P$34, X9.P$35, X9.P$36, X9.P$37, X9.P$38, X9.P$39, X9.P$40, X9.P$41, X9.P$42, X9.P$43, X9.P$44, X9.P$45, X9.P$46, X9.P$47, X9.P$48, X9.P$49, X9.P$50, X9.P$51, X9.P$52, X9.P$53, X9.P$54, X9.P$55, X9.P$56, X9.P$57, X9.P$58, X9.P$59, X9.P$60, X9.P$61, X9.P$62, X9.P$63, X9.P$64, X9.P$65, X9.P$66, X9.P$67
V3: R17.1, R129.1, TP26.P$1, X8.P$1, X8.P$2, X8.P$3, X8.P$4, X8.P$5, X8.P$6, X8.P$7, X8.P$8, X8.P$9, X8.P$10, X8.P$11, X8.P$12, X8.P$13, X8.P$14, X8.P$15, X8.P$16, X8.P$17, X8.P$18, X8.P$19, X8.P$20, X8.P$21, X8.P$22, X8.P$23, X8.P$24, X8.P$25, X8.P$26, X8.P$27, X8.P$28, X8.P$29, X8.P$30, X8.P$31, X8.P$32, X8.P$33, X8.P$34, X8.P$35, X8.P$36, X8.P$37, X8.P$38, X8.P$39, X8.P$40, X8.P$41, X8.P$42, X8.P$43, X8.P$44, X8.P$45, X8.P$46, X8.P$47, X8.P$48, X8.P$49, X8.P$50, X8.P$51, X8.P$52, X8.P$53, X8.P$54, X8.P$55, X8.P$56, X8.P$57, X8.P$58, X8.P$59, X8.P$60, X8.P$61, X8.P$62, X8.P$63, X8.P$64, X8.P$65, X8.P$66, X8.P$67
VBAT_FUSED: C41.2, D19.A, F2.T3 (F2), R43.2, T13.1 (S), T13.2 (S), T13.3 (S)
VSS_BAT: C7.2, C46.2, C49.2, C56.2, C59.2, C60.2, C168.2, C169.2, C171.2, C177.2, IC1.6 (VSS), IC1.P$1 (VSS), IC1.P$2 (VSS), IC26.17 (VSS), R48.1, R50.1, R138.1, R190.1, R192.1, T11.2 (S), T12.2 (S), TP29.P$1, X11.P$1, X11.P$2, X11.P$3, X11.P$4, X11.P$5, X11.P$6, X11.P$7, X11.P$8, X11.P$9, X11.P$10, X11.P$11, X11.P$12, X11.P$13, X11.P$14, X11.P$15, X11.P$16, X11.P$17, X11.P$18, X11.P$19, X11.P$20, X11.P$21, X11.P$22, X11.P$23, X11.P$24, X11.P$25, X11.P$26, X11.P$27, X11.P$28, X11.P$29, X11.P$30, X11.P$31, X11.P$32, X11.P$33, X11.P$34, X11.P$35, X11.P$36, X11.P$37, X11.P$38, X11.P$39, X11.P$40, X11.P$41, X11.P$42, X11.P$43, X11.P$44, X11.P$45, X11.P$46, X11.P$47, X11.P$48, X11.P$49, X11.P$50, X11.P$51, X11.P$52, X11.P$53, X11.P$54, X11.P$55, X11.P$56, X11.P$57, X11.P$58, X11.P$59, X11.P$60, X11.P$61, X11.P$62, X11.P$63, X11.P$64, X11.P$65, X11.P$66, X11.P$67, X14.2
V_PACK: C61.1, D4.C, D6.A, D8.A, R79.2, R218.2, R227.2, T14.1 (S), T14.2 (S), T14.3 (S), TP43.P$1, X13.5, X13.6, X13.7

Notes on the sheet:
STM32 1/2
STM32 SWD programming interface
7 x 4u7 25V
(5mR)
f_CLK = 10 ... 100 kHz
address: 0010010b
USB Type C Connector
Misc
Battery Charger
Changelog: 1.0 - initial release 1.1 - SPI-Flash added (IC3) - Debug connector X3 added - L1 replaced by WE-XHMI 74439358022 for f_S = 0.8 MHz instead of 1.2 MHz in order to increase efficiency - R52: 110k -> 137k - Update footprint of TPS65987D - R56: 110k -> 10k - R54, R55: 10k -> 1k8 - Redcubes 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
Changelog 1/3
f_SW = 600 kHz
f_CLK = 1 ... 2560 kHz
address: 1001111b
Temperature Sensors
internal pull-up @ EN-pin
+3V3 supply
3.267 V / 3.300 V / 3.333 V (min. / typ. / max.)
(4.7uH)
charge current limit = 5.4 A
Battery safety switch
Battery Monitor 1/2
f_CLK = 0 ... 400 kHz address: 0001000b
40 kR pull-up on PB4 enabled after reset
40 kR pull-up on PA13 & PA15 enabled after reset 40 kR pull-down on PA14 enabled after reset
X6 on bottom-layer X21 on top-layer
f_g = 160 Hz
Changelog 2/3
Changelog: 4.1 - X1 replaced by USB Type C receptacle - T6, T7 replaced by NPN transistor - R34, R88: 10M -> 1M - R46, R89: 4M7 -> 470k 4.2 - Testpoints added - Pads for connection of temperature sensor added 5.0 - STM32L071 replaced by STM32G071 - USB PD controller TPS65987DDHRSHR, Flash and Debug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
Second overvoltage protection
(10 A, slow-blow, 500 A interrupting rating)
Additional conventional fuse F1 because the Self Control Protector fuse F2 has a low interrupting rating of only 50 A
Delay time can be reduced for device testing by pulling CD to GND.
10k @ 25 °C 4M7 @ 100 °C
150044M155260: V_F,R,typ,5mA = 2.0 V V_F,G,typ,5mA = 2.7 V V_F,B,typ,5mA = 2.8 V
max. 6.5 V
2.4 V -> ACOK
Two 0R resistors for redundancy Can be removed for testing
Connector to load
STM32 2/2

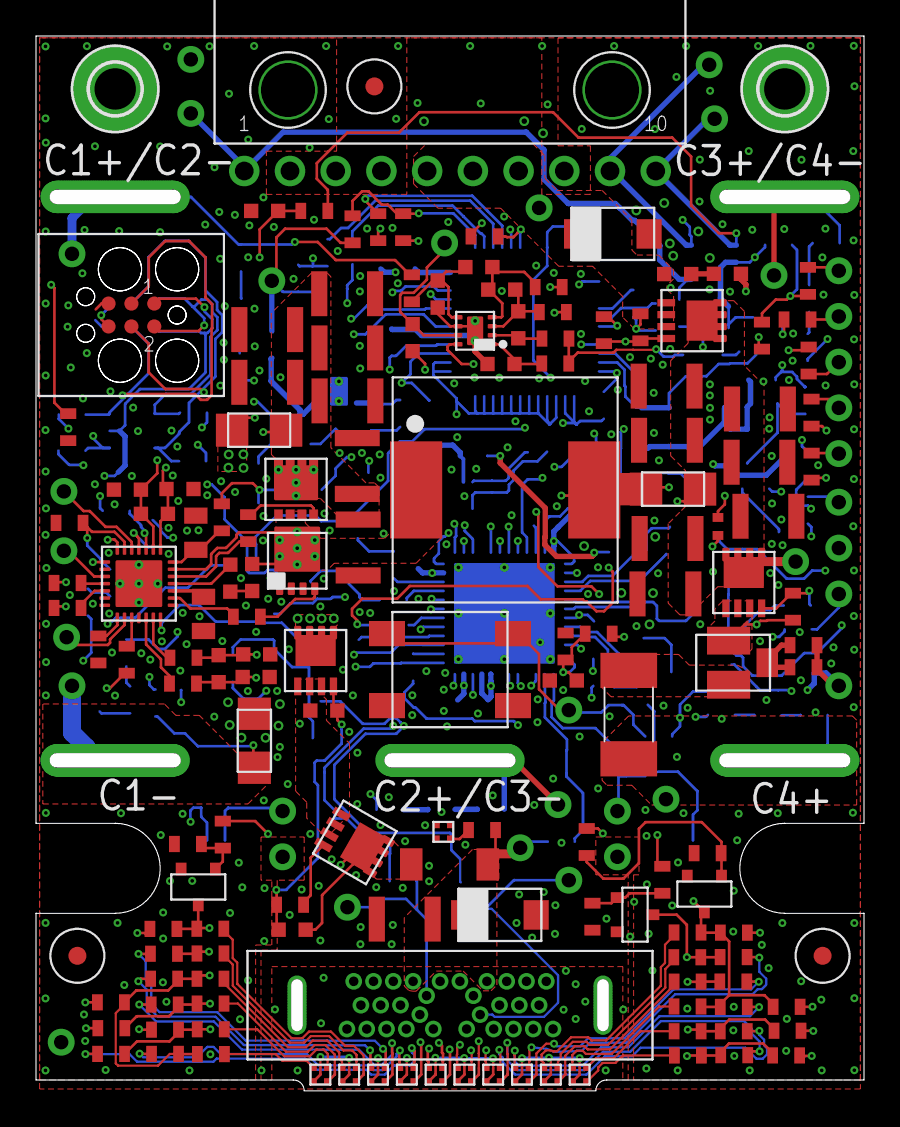
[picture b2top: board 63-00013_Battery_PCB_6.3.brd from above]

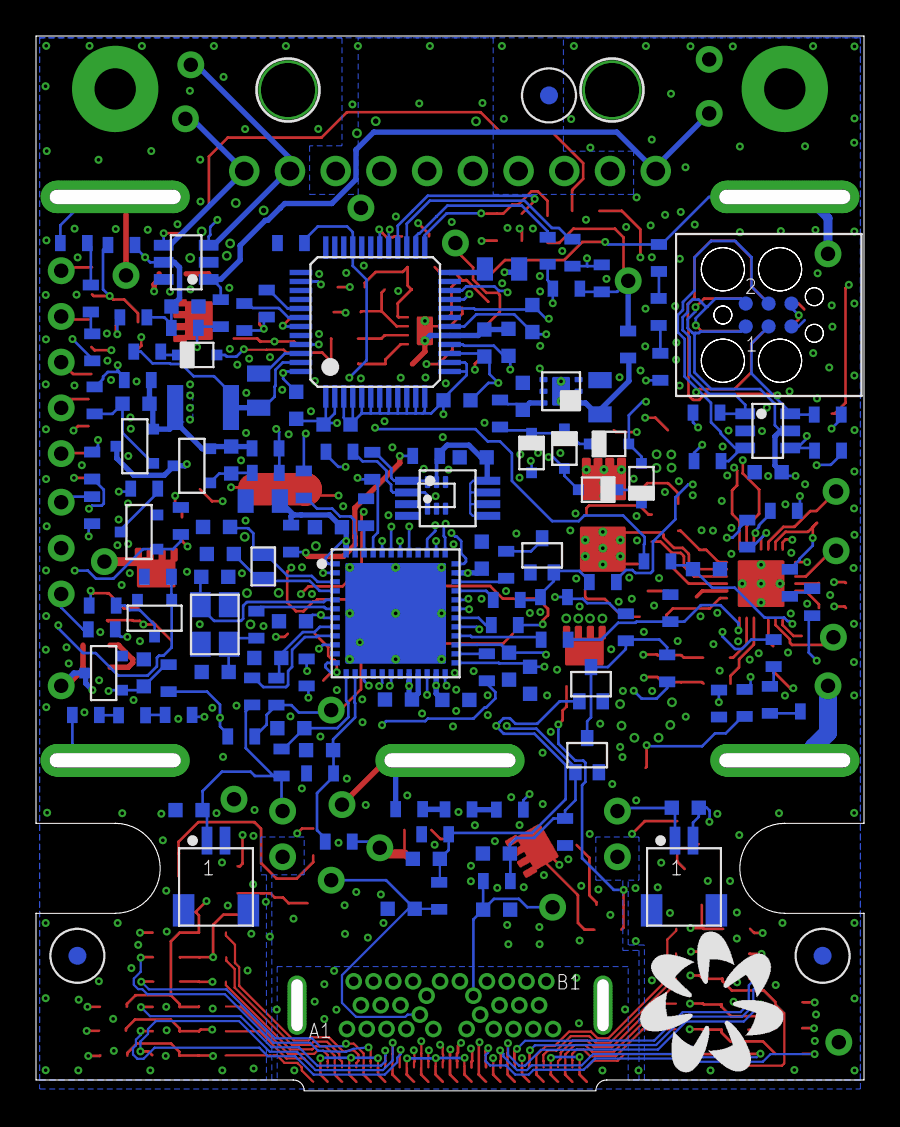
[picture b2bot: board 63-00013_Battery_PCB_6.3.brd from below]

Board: 4 copper layers, 46.0 x 58.6 mm, 339 parts (154 on the bottom side), 201 nets.
